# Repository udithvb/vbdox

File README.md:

DIY ergonomic keyboard clone "inspired" by Ergodox.

Source code for:
  1. PCB design in Kicad
  2. Keyboard layout using KLE.
  3. 3D model using Onshape
  4. Config files for KMK for firmware.

3D model files here https://cad.onshape.com/documents/ee7b6b641733c3f6c864279a/w/8fba0d1b41314f945c99cf82/e/c87f91dc97543009856402ba?renderMode=0&uiState=66990a0e6861fb6562c59a71

wiki:
	for flasing to rom hold bootsel before plugging -> mv to rpi folder
	for src code hold reset before plugging in + reset within 500ms -> mv to circuitpy folder

Use thonny, configure interpreter to circuipy generic device, uncomment debug to read serial console.

Rename boards for split to work:
	https://learn.adafruit.com/welcome-to-circuitpython/renaming-circuitpy

links for binaries:
	https://www.raspberrypi.com/documentation/microcontrollers/pico-series.html#resetting-flash-memory
	https://circuitpython.org/board/waveshare_rp2040_zero/
	https://github.com/KMKfw/kmk_firmware/blob/master/docs/en/Getting_Started.md

Edit config:
	Hold the reset key before plugging in, keep holding for 4 seconds after (topmost key on keeb) to get into the filesystem and edit config.

# Credits

-   Keyboard parts compiled by [joe-scotto ](https://github.com/joe-scotto/scottokeebs/tree/main/Extras/ScottoKicad).
-   Reversible hotswap sockets by [LouWii ](https://github.com/LouWii/ErgoMax/tree/master/libs).

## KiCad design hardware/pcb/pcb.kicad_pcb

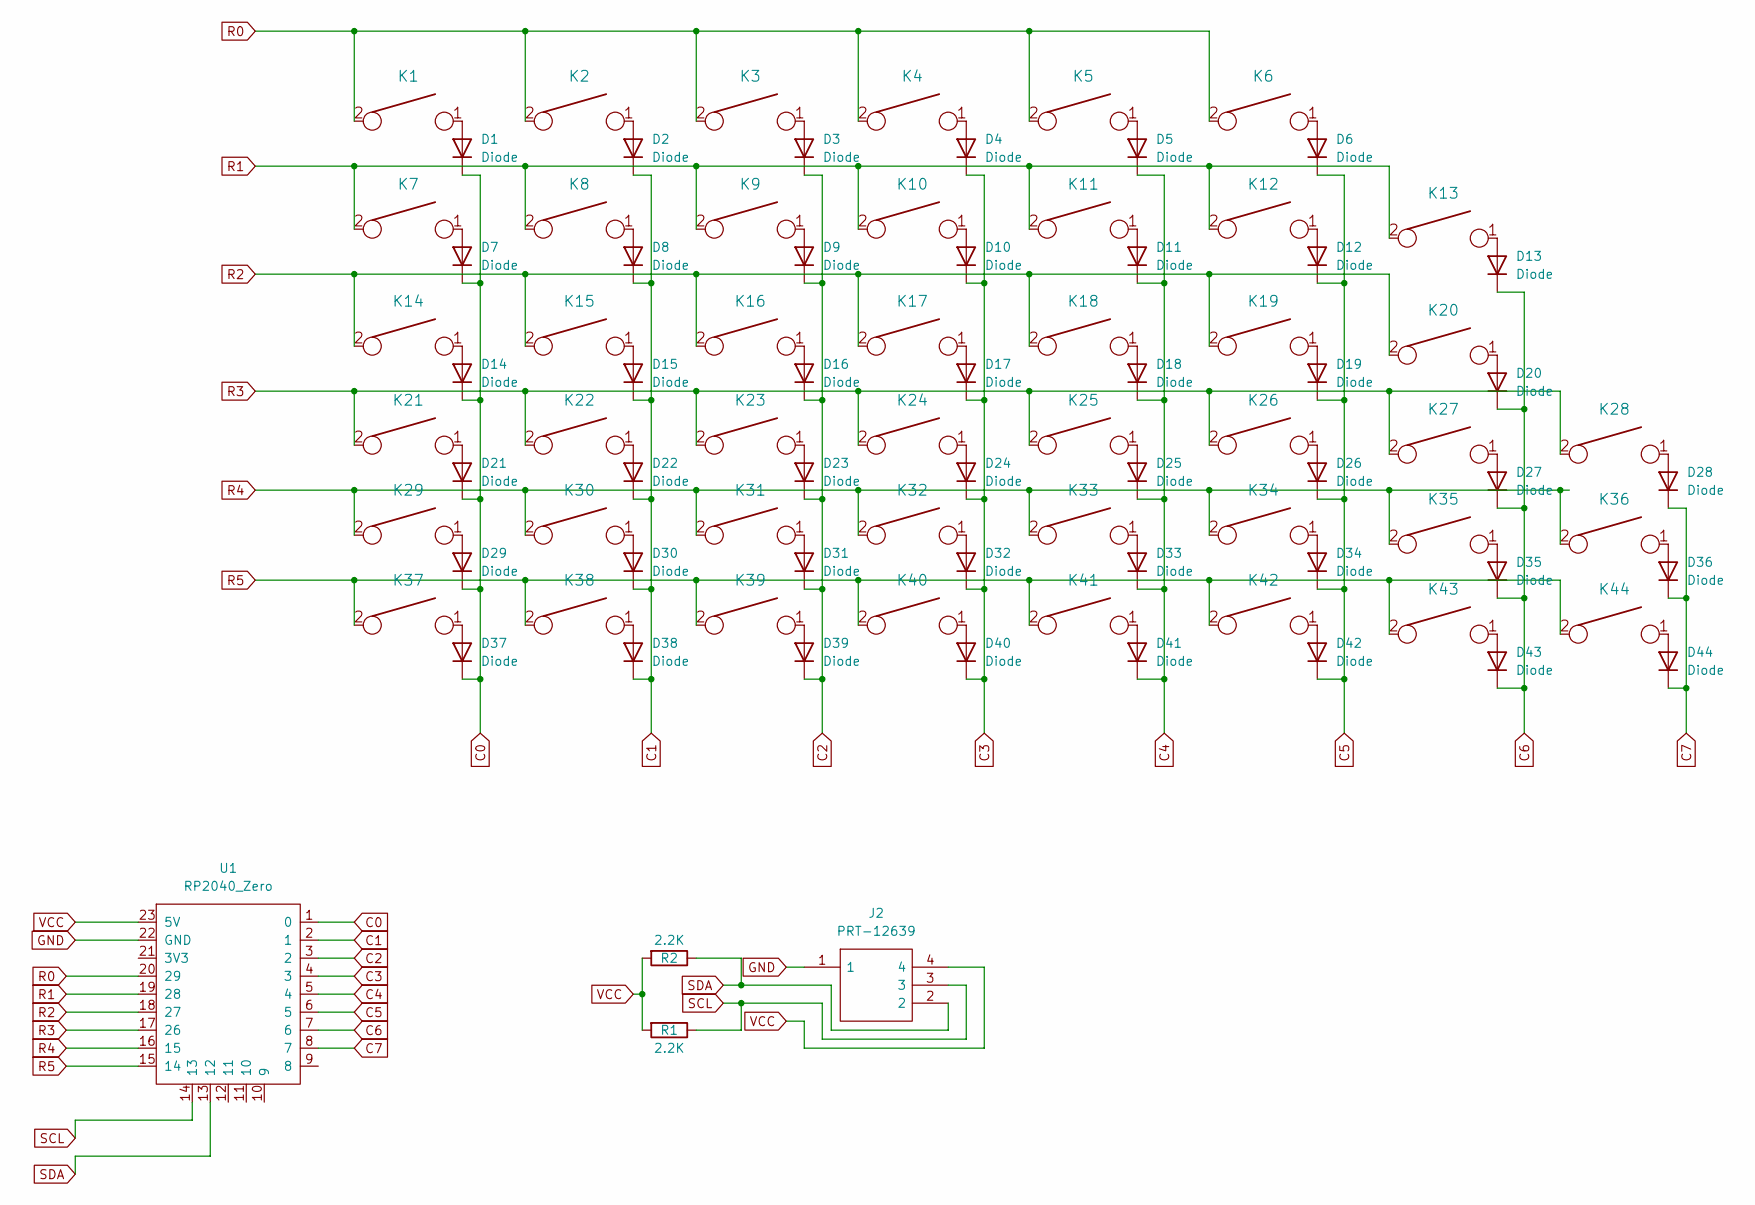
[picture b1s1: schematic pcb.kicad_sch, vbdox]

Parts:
D1, D2, D3, D4, D5, D6, D7, D8, D9, D10, D11, D12, D13, D14, D15, D16, D17, D18, D19, D20, D21, D22, D23, D24, D25, D26, D27, D28, D29, D30, D31, D32, D33, D34, D35, D36, D37, D38, D39, D40, D41, D42, D43, D44: Diode; Diode_DO-35
J2: PRT-12639; PRT12639; Mouser Part Number 474-PRT-12639
K1, K2, K3, K4, K5, K6, K7, K8, K9, K10, K11, K12, K13, K14, K15, K16, K17, K18, K19, K20, K21, K22, K23, K24, K25, K26, K27, K28, K29, K30, K31, K32, K33, K34, K35, K36, K37, K38, K39, K40, K41, K42, K43, K44: KEYSW; Kailh_MX_Socket_reversible
R1, R2: 2.2K; Diode_DO-35
U1: RP2040_Zero

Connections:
C0: D1.1 (K), D7.1 (K), D14.1 (K), D21.1 (K), D29.1 (K), D37.1 (K), U1.1 (0)
C1: D2.1 (K), D8.1 (K), D15.1 (K), D22.1 (K), D30.1 (K), D38.1 (K), U1.2 (1)
C2: D3.1 (K), D9.1 (K), D16.1 (K), D23.1 (K), D31.1 (K), D39.1 (K), U1.3 (2)
C3: D4.1 (K), D10.1 (K), D17.1 (K), D24.1 (K), D32.1 (K), D40.1 (K), U1.4 (3)
C4: D5.1 (K), D11.1 (K), D18.1 (K), D25.1 (K), D33.1 (K), D41.1 (K), U1.5 (4)
C5: D6.1 (K), D12.1 (K), D19.1 (K), D26.1 (K), D34.1 (K), D42.1 (K), U1.6 (5)
C6: D13.1 (K), D20.1 (K), D27.1 (K), D35.1 (K), D43.1 (K), U1.7 (6)
C7: D28.1 (K), D36.1 (K), D44.1 (K), U1.8 (7)
GND: U1.22 (GND); also elsewhere on the board
unnamed: D1.2 (A), K1.1
unnamed: D2.2 (A), K2.1
unnamed: D3.2 (A), K3.1
unnamed: D4.2 (A), K4.1
unnamed: D5.2 (A), K5.1
unnamed: D6.2 (A), K6.1
unnamed: D7.2 (A), K7.1
unnamed: D8.2 (A), K8.1
unnamed: D9.2 (A), K9.1
unnamed: D10.2 (A), K10.1
unnamed: D11.2 (A), K11.1
unnamed: D12.2 (A), K12.1
unnamed: D13.2 (A), K13.1
unnamed: D14.2 (A), K14.1
unnamed: D15.2 (A), K15.1
unnamed: D16.2 (A), K16.1
unnamed: D17.2 (A), K17.1
unnamed: D18.2 (A), K18.1
unnamed: D19.2 (A), K19.1
unnamed: D20.2 (A), K20.1
unnamed: D21.2 (A), K21.1
unnamed: D22.2 (A), K22.1
unnamed: D23.2 (A), K23.1
unnamed: D24.2 (A), K24.1
unnamed: D25.2 (A), K25.1
unnamed: D26.2 (A), K26.1
unnamed: D27.2 (A), K27.1
unnamed: D28.2 (A), K28.1
unnamed: D29.2 (A), K29.1
unnamed: D30.2 (A), K30.1
unnamed: D31.2 (A), K31.1
unnamed: D32.2 (A), K32.1
unnamed: D33.2 (A), K33.1
unnamed: D34.2 (A), K34.1
unnamed: D35.2 (A), K35.1
unnamed: D36.2 (A), K36.1
unnamed: D37.2 (A), K37.1
unnamed: D38.2 (A), K38.1
unnamed: D39.2 (A), K39.1
unnamed: D40.2 (A), K40.1
unnamed: D41.2 (A), K41.1
unnamed: D42.2 (A), K42.1
unnamed: D43.2 (A), K43.1
unnamed: D44.2 (A), K44.1
R0: K1.2, K2.2, K3.2, K4.2, K5.2, K6.2, U1.20 (29)
R1: K7.2, K8.2, K9.2, K10.2, K11.2, K12.2, K13.2, U1.19 (28)
R2: K14.2, K15.2, K16.2, K17.2, K18.2, K19.2, K20.2, U1.18 (27)
R3: K21.2, K22.2, K23.2, K24.2, K25.2, K26.2, K27.2, K28.2, U1.17 (26)
R4: K29.2, K30.2, K31.2, K32.2, K33.2, K34.2, K35.2, K36.2, U1.16 (15)
R5: K37.2, K38.2, K39.2, K40.2, K41.2, K42.2, K43.2, K44.2, U1.15 (14)
VCC: R1.2, R2.2, U1.23 (5V); also elsewhere on the board

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
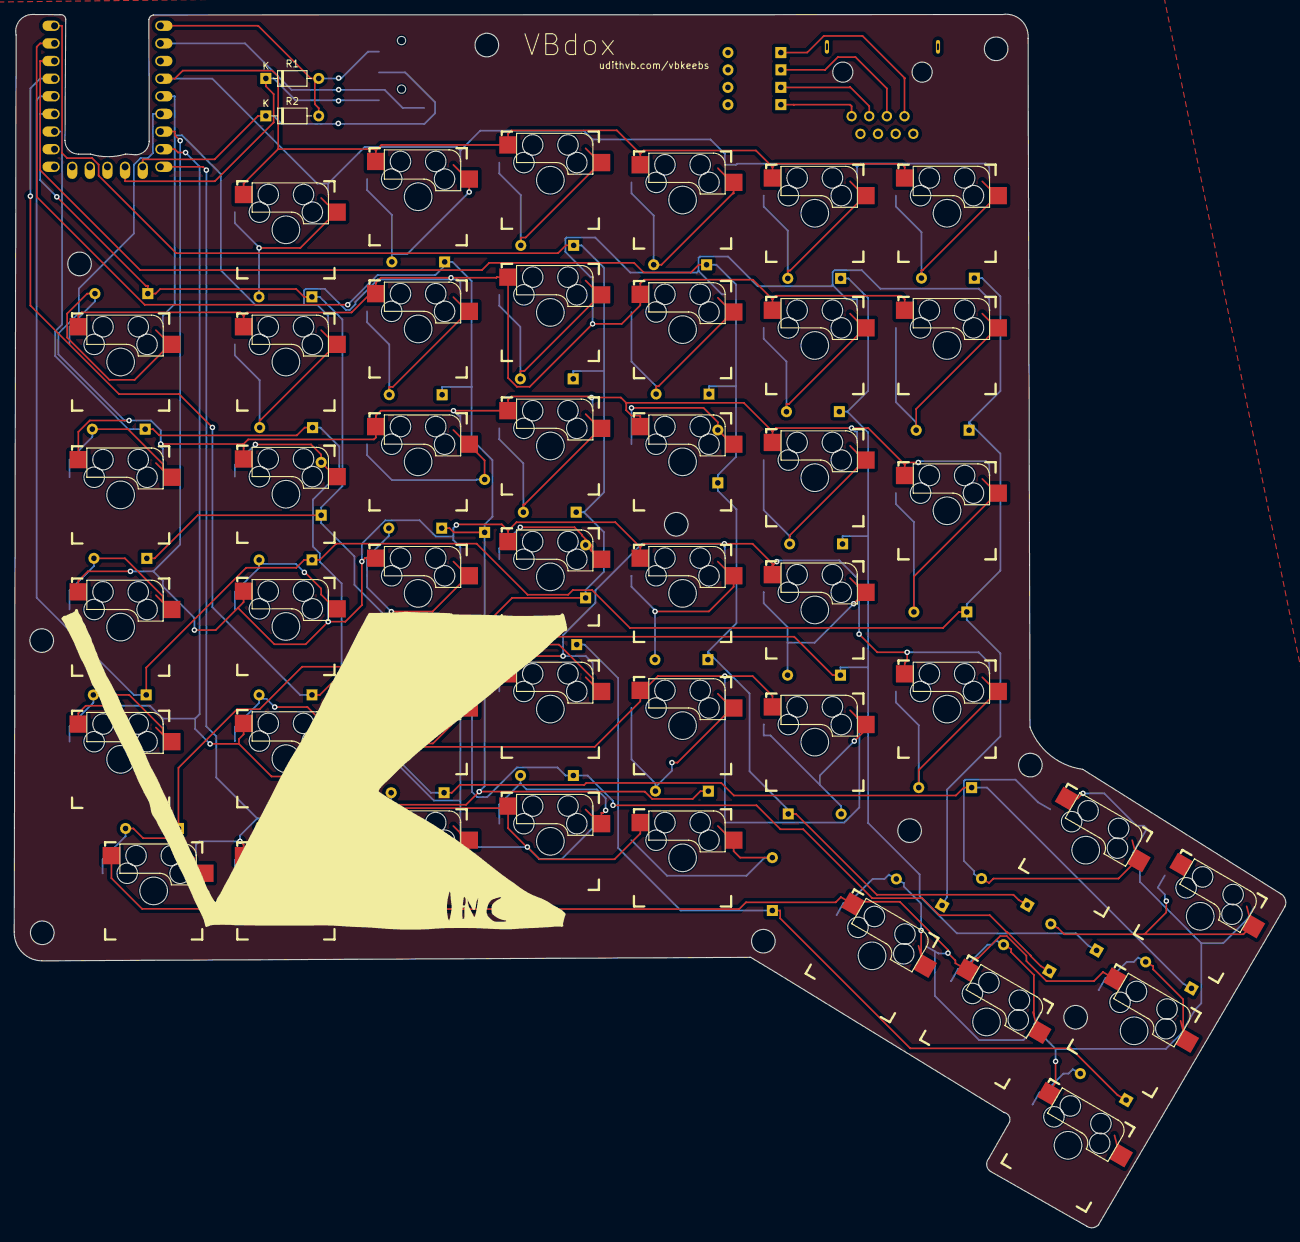
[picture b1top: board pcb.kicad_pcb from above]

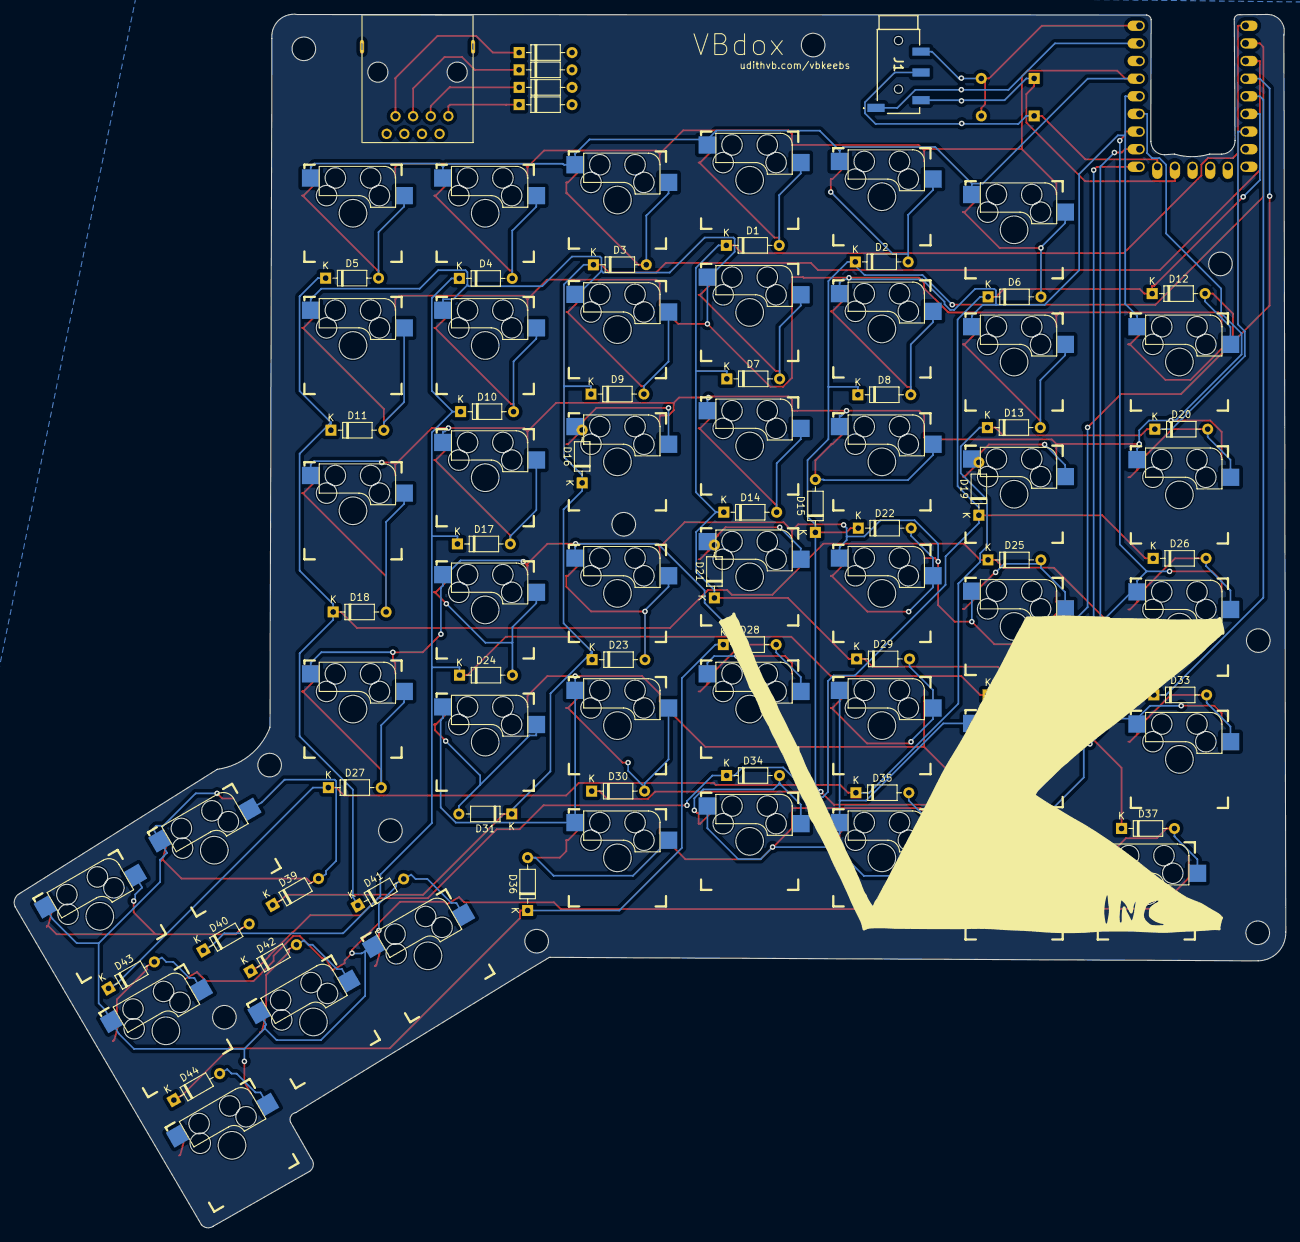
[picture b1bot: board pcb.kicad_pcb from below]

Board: 2 copper layers, 183.2 x 174.8 mm, 92 parts (46 on the bottom side), 62 nets.

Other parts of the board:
J1: PRT-12639; PRT12639

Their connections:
GND: J1.1; also elsewhere on the board
VCC: J1.4; also elsewhere on the board

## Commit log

2023-10-27 init kicad project
2023-10-27 added kicad libs
2023-10-29 added 6X8 matrix and global labels
2023-10-29 schema init
2023-10-31 placed switched to ergomax layout using plugin, and added edge cuts for castelled rp2040 zero
2023-11-01 routing
2023-11-02 left side layout in kle
2023-11-17 rj45 jack instead of trrs
2023-11-18 removed outline, to add rj45
2023-11-18 prod
2024-02-11 PCB step file
2024-02-11 miryoku init
2024-02-14 home row mods L
2024-02-14 number row added ]+\
2024-02-14 cleaned up LAYER_TEMPLATE
2024-02-14 nav layer
2024-02-14 nav layer home,pgup,pgdown,end
2024-02-14 symbol layer
2024-02-16 tap_time parametric
2024-02-17 fix { instead of }
2024-02-17 mouse layer init, boot.py to remove automount and enable mouse panning
2024-02-17 mouse layer
2024-02-24 kle files reorg
2024-07-18 draft readme
2024-07-18 added photo
2024-11-01 better docs and binnaries with links
2024-11-09 tmux and i3 keys
